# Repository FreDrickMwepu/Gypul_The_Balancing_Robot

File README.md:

# Robo Core Zambia

<p align="center">

</p>

## The Vision 🎯

I've been working on creating **RoboCore Zambia** — a locally engineered, modular robotics and embedded systems development platform designed for STEM education across Zambia and Africa. The goal is ambitious but necessary: build an affordable, open-source platform that enables educators and makers to teach robotics, IoT, and embedded systems design without relying on expensive imported kits (which typically cost $120–$700 or more, before shipping and customs).

RoboCore Zambia isn't a single application — it's a flexible foundation. Self-balancing robots, autonomous vehicles, drone controllers, IoT sensors, and wireless communication projects are all possible with the same core platform.

<p align="center">
	
	<br><em>Early prototype demonstrating the RoboCore Zambia platform</em>
</p>

The platform includes:
- 🧠 ESP32 microcontroller for processing and wireless communication
- 📡 IMU sensors (MPU-6050) for motion sensing and orientation tracking
- 🔌 Dual H-bridge motor drivers with high-current capability
- 🧩 Custom 2-layer PCB for integrated control and reliability
- 🧱 Modular connectors for motors, sensors, and expansions
- 🏭 Open-source design files for local manufacturing and customization

---

## Table of Contents 🗂️

- [The Vision](#the-vision-)
- [Why This Matters](#why-this-matters-)
- [Showcase Gallery](#showcase-gallery-)
- [The Reality Check](#the-reality-check-)
- [My Learning Curve](#my-learning-curve-)
- [How You Can Help](#how-you-can-help-)
- [The Bigger Picture](#the-bigger-picture-)
- [Next Steps](#next-steps-)
- [Get Involved](#get-involved-)
- [Final Thoughts](#final-thoughts-)

## Why This Matters 🌍

Since 2022, I've had the incredible privilege of impacting over 8000+ young people across Zambia through various programs covering digital literacy, robotics, and Artificial Intelligence. Every time I run these sessions, I see the same thing: brilliant, curious minds hungry to learn and create, but limited by access to affordable tools and platforms.

Most robotics kits are either impossible to import affordably to our markets or simply don't exist here. When they do make it through, the costs are prohibitive for most students, schools, and even makerspaces. This project aims to change that by creating something locally relevant, affordable, and designed specifically for our context.

## Showcase Gallery 📸

<details>
	<summary>More photos</summary>
	
</details>

---

## The Reality Check 🧪

Here's where I get honest about my learning journey (and current challenges):

**What's Working ✅:**

The core platform is functional! I've successfully built working prototypes and validated the PCB design with real-world testing. The ESP32-based control system, motor drivers, and IMU sensor integration all perform as expected. The modularity of the design means the same platform has been used for multiple applications beyond self-balancing robots.

<p align="center">
	
	<br><em>Robot balancing in action</em>
</p>

**What's Not Working ⚠️:**
- Some mechanical designs need optimization for different applications (weight distribution, center of gravity)
- Sensor calibration requires careful tuning depending on the specific use case
- Documentation and example code could be more comprehensive for different robot designs

**What's Still in Development 🛠️:**
- Expanding example code and tutorials for different robotics applications
- Developing reference designs for various platforms (balancing robots, autonomous rovers, drone controllers)
- Creating comprehensive educational resources and lesson plans
- Building a community repository of user-contributed designs and modifications

<p align="center">
	
	<br><em>PCB and mechanical design concepts</em>
</p>

## My Learning Curve 📈

I should be upfront: I'm no expert in any of these technical branches. 3D modeling, PCB design, control systems, embedded programming - this project and others I've worked on have all been massive learning experiences. Every "failure" has taught me something valuable, but I've definitely hit the point where I could use guidance from people who've walked this path before.

This isn't about admitting defeat - it's about recognizing that complex projects benefit from community knowledge and collaboration. Some of my best learning has come from bouncing ideas off people who see things I miss or approach problems differently.

## How You Can Help 🤝

I'm looking for any kind of support, and it doesn't have to be a huge commitment:

**Technical Guidance 🛠️:**
- PCB design feedback, manufacturing best practices, and component selection
- Embedded systems and firmware optimization
- Mechanical design and 3D printing techniques
- Educational curriculum integration for robotics and embedded systems
- Code review for control algorithms and sensor fusion

**Knowledge Sharing 📚:**
- Pointing me toward useful resources, tutorials, or documentation
- Sharing your own project experiences and lessons learned
- Connecting me with others who might be interested in collaborating

**Brainstorming 🧠:**
- Manufacturing and scaling strategies
- Educational curriculum integration ideas
- Distribution and partnership opportunities

**Community Building 🌱:**
- Spreading the word about the project
- Connecting me with educational institutions or maker communities
- Sharing this with anyone who might be interested in African tech innovation

## The Bigger Picture 🌐

This isn't just about building robotics projects — it's about creating an open-source, locally relevant development platform that enables education and innovation across the continent. The vision includes:

- Open-source hardware and firmware that others can fork, modify, and improve
- Educational resources, tutorials, and reference designs for common applications
- Partnerships with schools, universities, and maker spaces for curriculum integration
- A pathway for local component sourcing and PCB fabrication across African regions
- Community-driven documentation and a repository of user projects and innovations

Every learning moment, every component test, every design iteration gets us closer to something that can genuinely impact how young people across Africa engage with technology and innovation.

## Electronics & Hardware Design

### Overview

To move the project beyond breadboards and jump-wires we designed a custom 2-layer PCB in KiCad. The board replaces fragile prototype wiring to improve reliability, reduce assembly time, and lower per-unit costs — all important for classroom and makerspace use.

### Key Subsystems

- **Processing & Control:** ESP32-WROOM module providing Wi‑Fi, Bluetooth, and Arduino-compatible development for students and makers.
- **Motion Sensing:** MPU‑6050 IMU (3‑axis gyroscope + 3‑axis accelerometer) used for balance sensing and closed‑loop control.
- **Motor Control:** Dual H‑bridge motor drivers with dedicated high‑current copper traces and thermal considerations for continuous operation.
- **Power Management:** LiPo battery support with a USB Type‑C charging input, onboard voltage regulators, and reverse‑polarity protection to protect classroom hardware.
- **Memory:** Onboard flash for firmware and simple data logging (sensor logs, calibration presets).
- **Connectivity & Expansion:** Standard I2C, SPI, and UART breakout headers plus modular connectors (J2, J3, J4) for motors and external sensors to keep the design flexible.

### Design Decisions

- Chosen parts prioritize local availability and low BOM complexity to make sourcing components easier in Zambia and nearby markets.
- A continuous ground plane and careful keep‑out were used around the ESP32 antenna to preserve wireless performance.
- Power traces for motors were routed and sized separately from logic power to reduce noise and avoid voltage drops during high current draw.
- Breakout headers and modular connectors were added to encourage experimentation and easy repairs in an educational setting.

### Toolchain

The PCB was designed in KiCad. 3D renders were generated from the PCB model to validate component placement and mechanical fit before fabrication.

### Status

The board is at Revision 1 and currently in fabrication and early testing. Feedback from these tests will guide revisions to the layout and BOM.

For full schematics, PCB layout files, and fabrication notes see the project hardware folder: [PCB-Design](PCB-Design).

### Board Renders

<em>Top and bottom 3D renders of the RoboCore PCB. Replace these placeholder files with the actual KiCad export renders in the `PCB-Design` folder.</em>

## Get Involved 📣

If any of this resonates with you - whether you're a technical expert, educator, maker, or just someone who believes in making technology more accessible - I'd love to connect.

You can reach me through:
- This platform (just send a message!)
- Website: [www.plastalbotbuilders.com](https://plastalbot.comon.tech/home)
- Email: fredrickmwepu22@gmail.com

Even if you can't directly contribute technical expertise, sharing this project, connecting me with others, or just offering encouragement makes a real difference.

## Final Thoughts 💡

Building RoboCore Zambia has been humbling, educational, and incredibly motivating. Every challenge reminds me why this work matters — because somewhere, a young person is waiting for the chance to learn, build, and innovate, and we have the opportunity to make that possible.

<p align="center">
	
	<br><em>Click image to watch a short demo video</em>
</p>

Thanks for taking the time to read this, and thanks in advance for any way you choose to support this journey. Together, we can build an open-source robotics platform that empowers the next generation of African innovators, engineers, and educators.

---

*This project represents just one piece of the larger puzzle of making technology education accessible across Africa. Every contribution, no matter how small, helps build that future.*

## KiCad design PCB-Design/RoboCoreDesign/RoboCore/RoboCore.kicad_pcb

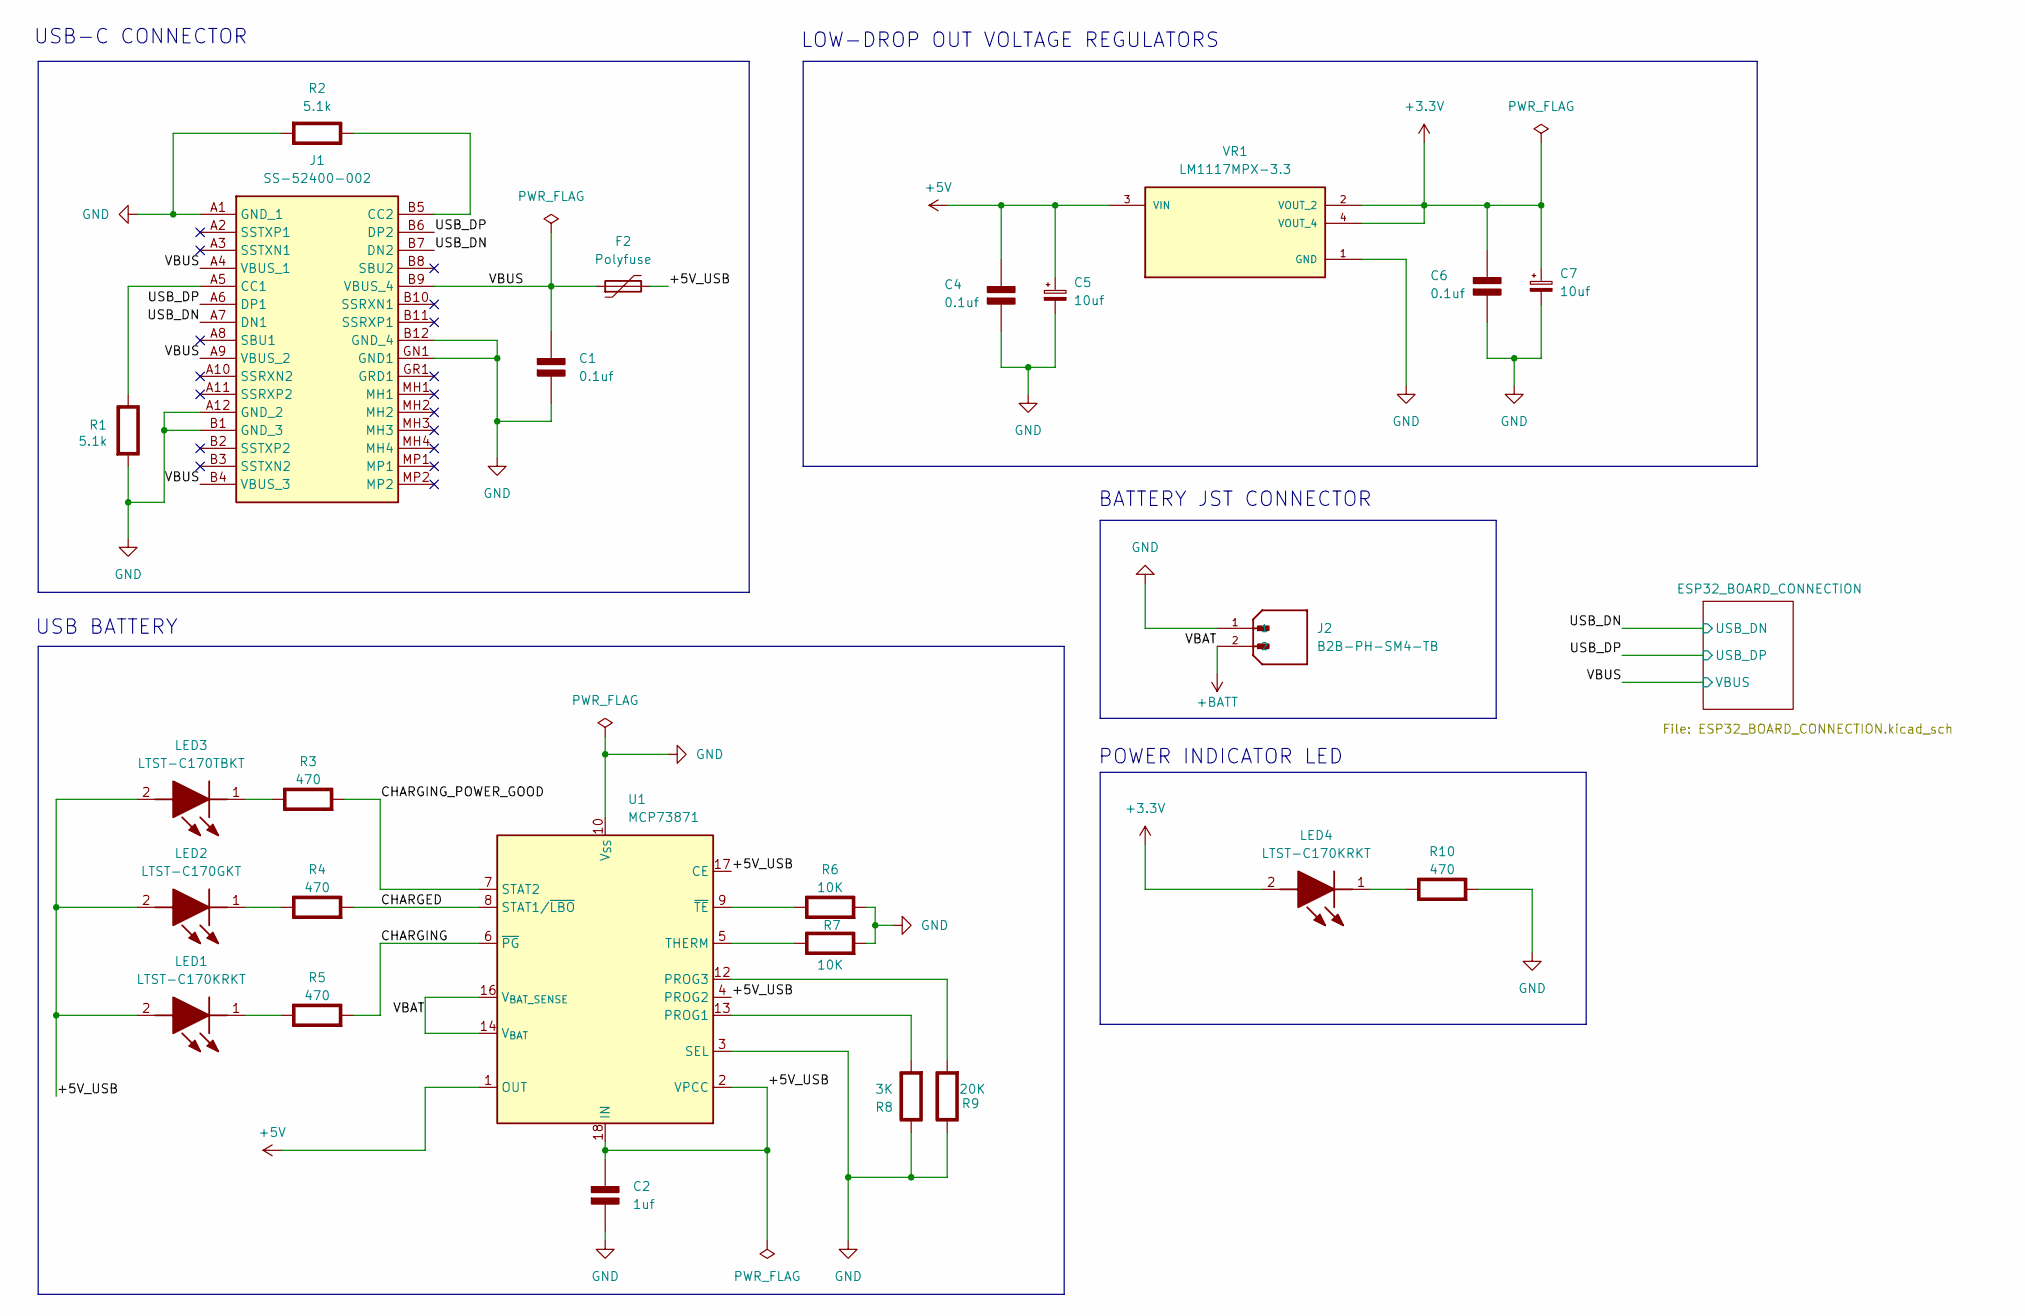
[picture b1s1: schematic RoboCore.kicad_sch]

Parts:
C1, C4, C6: 0.1uf; C_0805_2012Metric; Rating V
C2: 1uf; C_0805_2012Metric; Rating V
C5, C7: 10uf; T491A
F2: Polyfuse; FUSSC324X455X250-2N
J1: SS-52400-002; SS52400002; Manufacturer_Part_Number SS-52400-002; Mouser Part Number 530-SS-52400-002
J2: B2B-PH-SM4-TB; JST_B2B-PH-SM4-TB; PARTREV N/A
LED1, LED4: LTST-C170KRKT; LEDC2012X120N; Manufacturer_Part_Number LTST-C170KRKT; Mouser Part Number 859-LTST-C170KRKT
LED2: LTST-C170GKT; LEDC2012X120N; Manufacturer_Part_Number LTST-C170GKT; Mouser Part Number 859-LTST-C170GKT
LED3: LTST-C170TBKT; LEDC2012X120N; Manufacturer_Part_Number LTST-C170TBKT; Mouser Part Number 859-LTST-C170TBKT
R1, R2: 5.1k; R_0805_2012Metric; Rating W
R3, R4, R5, R10: 470; R_0805_2012Metric; Rating W
R6, R7: 10K; R_0805_2012Metric; Rating W
R8: 3K; R_0805_2012Metric; Rating W
R9: 20K; R_0805_2012Metric; Rating W
U1: MCP73871; QFN-20-1EP_4x4mm_P0.5mm_EP2.5x2.5mm
VR1: LM1117MPX-3.3; VREG_LM1117MPX-3.3_NOPB

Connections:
+5V: C4.1 (+), C5.1, U1.1 (OUT), U1.20 (OUT), VR1.3 (VIN)
/+5V_USB: C2.1 (+), F2.2, LED1.2 (A), LED2.2 (A), LED3.2 (A), U1.2 (VPCC), U1.4 (PROG2), U1.17 (CE), U1.18 (IN), U1.19 (IN)
/CHARGED: R4.2 (-), U1.8 (STAT1/~LBO)
/CHARGING: R5.2 (-), U1.6 (~PG)
/CHARGING_POWER_GOOD: R3.2 (-), U1.7 (STAT2)
/USB_DN: J1.A7 (DN1), J1.B7 (DN2); also elsewhere on the board
/USB_DP: J1.A6 (DP1), J1.B6 (DP2); also elsewhere on the board
/VBAT: J2.2, U1.14 (V_{BAT}), U1.15 (V_{BAT}), U1.16 (V_{BAT_SENSE})
/VBUS: C1.1 (+), F2.1, J1.A4 (VBUS_1), J1.A9 (VBUS_2), J1.B4 (VBUS_3), J1.B9 (VBUS_4); also elsewhere on the board
unnamed: J1.A5 (CC1), R1.1 (+)
unnamed: J1.B5 (CC2), R2.1 (+)
unnamed: LED1.1 (K), R5.1 (+)
unnamed: LED2.1 (K), R4.1 (+)
unnamed: LED3.1 (K), R3.1 (+)
unnamed: LED4.1 (K), R10.1 (+)
unnamed: R6.1 (+), U1.9 (~TE)
unnamed: R7.1 (+), U1.5 (THERM)
unnamed: R8.2 (-), U1.13 (PROG1)
unnamed: R9.2 (-), U1.12 (PROG3)

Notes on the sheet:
USB BATTERY
POWER INDICATOR LED
BATTERY JST CONNECTOR
LOW-DROP OUT VOLTAGE REGULATORS
USB-C CONNECTOR

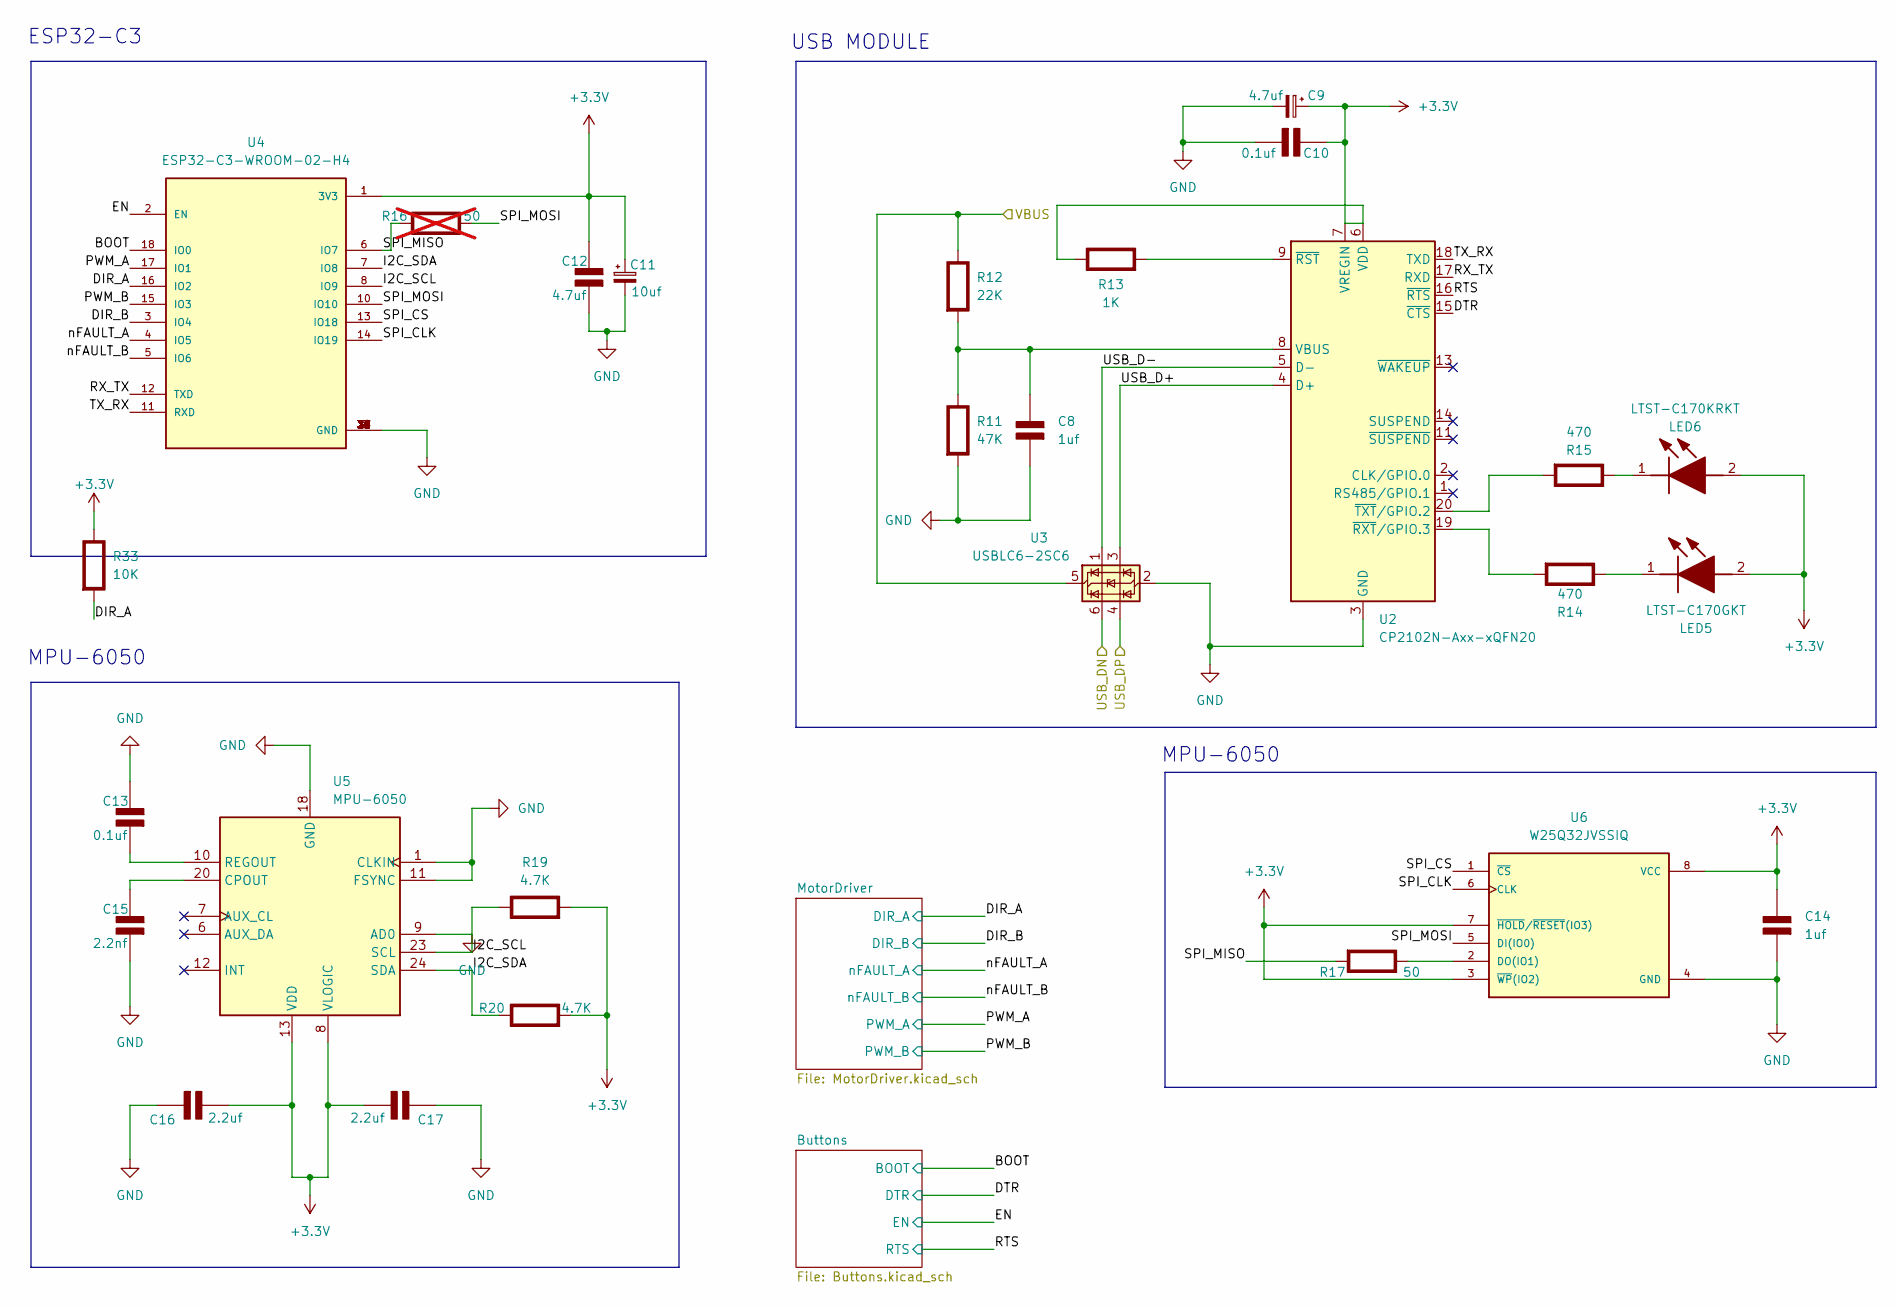
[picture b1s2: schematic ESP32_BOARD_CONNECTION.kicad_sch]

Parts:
C8, C14: 1uf; C_0805_2012Metric; Rating V
C9: 4.7uf; T491A
C10, C13: 0.1uf; C_0805_2012Metric; Rating V
C11: 10uf; T491A
C12: 4.7uf; C_0805_2012Metric; Rating V
C15: 2.2nf; C_0805_2012Metric; Rating V
C16, C17: 2.2uf; C_0805_2012Metric; Rating V
LED5: LTST-C170GKT; LEDC2012X120N; Manufacturer_Part_Number LTST-C170GKT; Mouser Part Number 859-LTST-C170GKT
LED6: LTST-C170KRKT; LEDC2012X120N; Manufacturer_Part_Number LTST-C170KRKT; Mouser Part Number 859-LTST-C170KRKT
R11: 47K; R_0805_2012Metric; Rating W
R12: 22K; R_0805_2012Metric; Rating W
R13: 1K; R_0805_2012Metric; Rating W
R14, R15: 470; R_0805_2012Metric; Rating W
R16: 50; R_0805_2012Metric; Rating W; not fitted
R17: 50; R_0805_2012Metric; Rating W
R19, R20: 4.7K; R_0805_2012Metric; Rating W
R33: 10K; R_0805_2012Metric
U2: CP2102N-Axx-xQFN20; QFN50P400X400X100-21N-D
U3: USBLC6-2SC6; SOT-23-6
U4: ESP32-C3-WROOM-02-H4; MODULE_ESP32-C3-WROOM-02-H4
U5: MPU-6050; InvenSense_QFN-24_4x4mm_P0.5mm
U6: W25Q32JVSSIQ; SOIC127P790X216-8N; M_PART_NUMBER W25QXX

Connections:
/ESP32_BOARD_CONNECTION/BOOT: U4.18 (IO0); also elsewhere on the board
/ESP32_BOARD_CONNECTION/DIR_A: R33.2 (-), U4.16 (IO2); also elsewhere on the board
/ESP32_BOARD_CONNECTION/DIR_B: U4.3 (IO4); also elsewhere on the board
/ESP32_BOARD_CONNECTION/DTR: U2.15 (~CTS); also elsewhere on the board
/ESP32_BOARD_CONNECTION/EN: U4.2 (EN); also elsewhere on the board
/ESP32_BOARD_CONNECTION/PWM_A: U4.17 (IO1); also elsewhere on the board
/ESP32_BOARD_CONNECTION/PWM_B: U4.15 (IO3); also elsewhere on the board
/ESP32_BOARD_CONNECTION/RTS: U2.16 (~RTS); also elsewhere on the board
/ESP32_BOARD_CONNECTION/RX_TX: U2.17 (RXD), U4.12 (TXD)
/ESP32_BOARD_CONNECTION/SPI_CLK: U4.14 (IO19), U6.6 (CLK)
/ESP32_BOARD_CONNECTION/SPI_CS: U4.13 (IO18), U6.1 (~CS)
/ESP32_BOARD_CONNECTION/SPI_MOSI: R16.2 (-), U4.10 (IO10), U6.5 (DI(IO0))
/ESP32_BOARD_CONNECTION/TX_RX: U2.18 (TXD), U4.11 (RXD)
/ESP32_BOARD_CONNECTION/USB_D+: U2.4 (D+), U3.3 (I/O2)
/ESP32_BOARD_CONNECTION/USB_D-: U2.5 (D-), U3.1 (I/O1)
/ESP32_BOARD_CONNECTION/nFAULT_A: U4.4 (IO5); also elsewhere on the board
/ESP32_BOARD_CONNECTION/nFAULT_B: U4.5 (IO6); also elsewhere on the board
/USB_DN: U3.6 (I/O1); also elsewhere on the board
/USB_DP: U3.4 (I/O2); also elsewhere on the board
/VBUS: R12.1 (+), U3.5 (VBUS); also elsewhere on the board
unnamed: C8.2 (-), R11.1 (+), R12.2 (-), U2.8 (VBUS)
unnamed: C13.1 (+), U5.10 (REGOUT)
unnamed: C15.2 (-), U5.20 (CPOUT)
unnamed: LED5.1 (K), R14.1 (+)
unnamed: LED6.1 (K), R15.1 (+)
unnamed: R13.2 (-), U2.9 (~RST)
unnamed: R14.2 (-), U2.19 (~RXT/GPIO.3)
unnamed: R15.2 (-), U2.20 (~TXT/GPIO.2)
unnamed: R17.1 (+), U6.2 (DO(IO1))

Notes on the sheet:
USB MODULE
ESP32-C3
MPU-6050

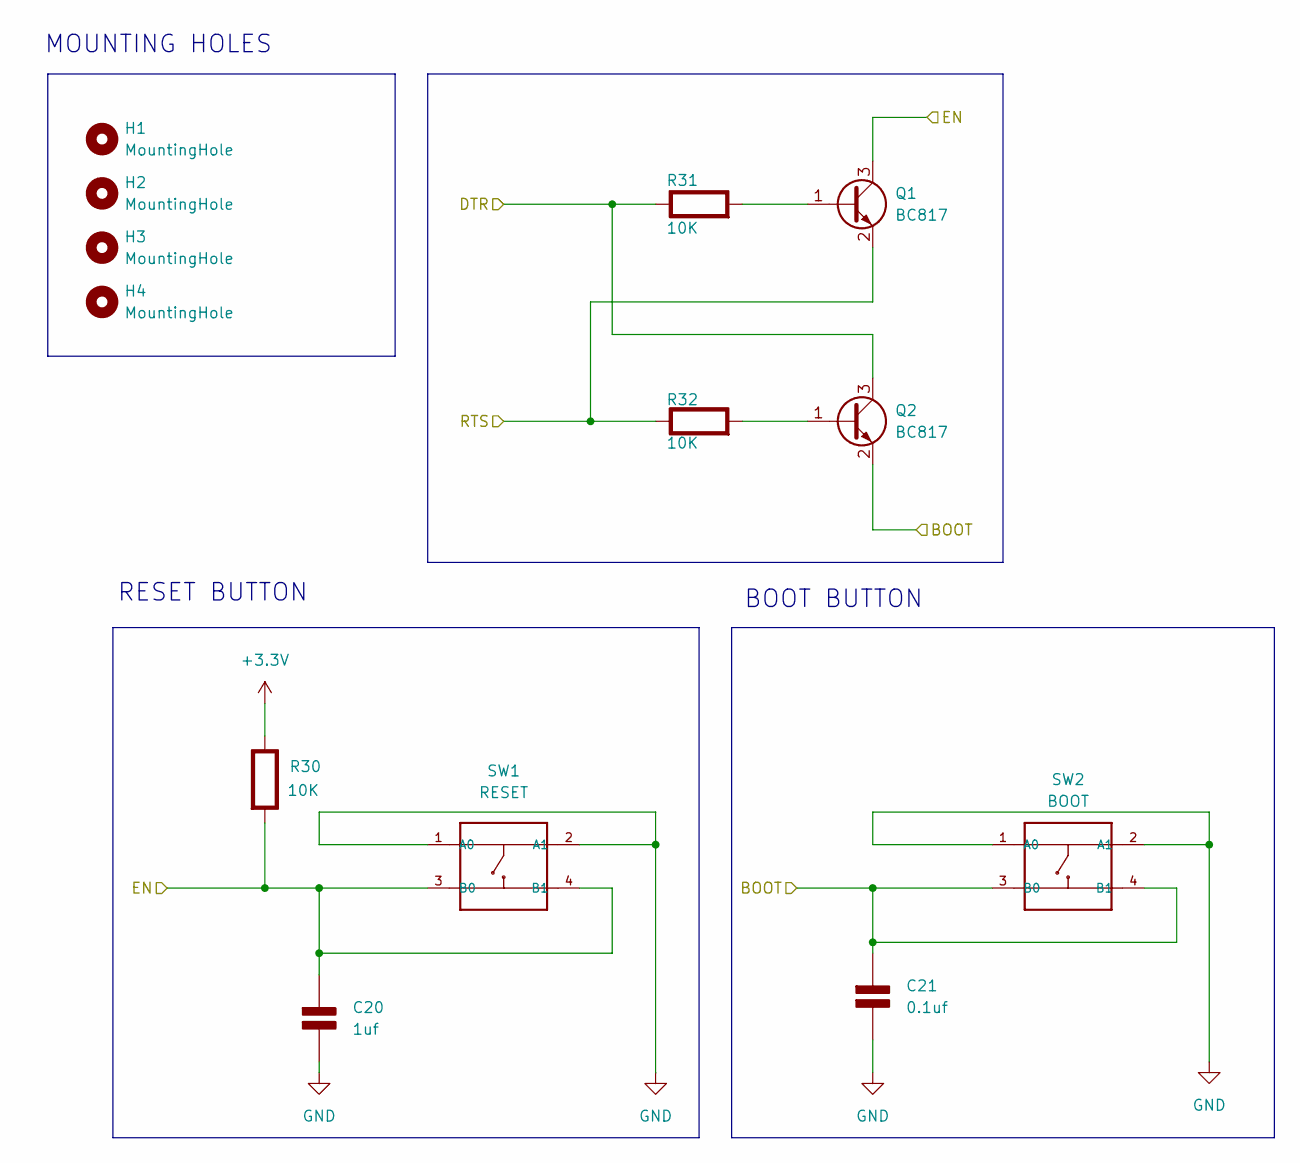
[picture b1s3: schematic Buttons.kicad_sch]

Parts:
C20: 1uf; C_0805_2012Metric; Rating V
C21: 0.1uf; C_0805_2012Metric; Rating V
H1, H2, H3, H4: MountingHole; MountingHole_2mm
Q1, Q2: BC817; SOT-23
R30, R31, R32: 10K; R_0805_2012Metric; Rating W
SW1: RESET; SW4-SMD-5.2X5.2X1.5MM
SW2: BOOT; SW4-SMD-5.2X5.2X1.5MM

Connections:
/ESP32_BOARD_CONNECTION/BOOT: C21.1 (+), Q2.2 (E), SW2.3 (B0), SW2.4 (B1); also elsewhere on the board
/ESP32_BOARD_CONNECTION/DTR: Q2.3 (C), R31.1 (+); also elsewhere on the board
/ESP32_BOARD_CONNECTION/EN: C20.1 (+), Q1.3 (C), R30.2 (-), SW1.3 (B0), SW1.4 (B1); also elsewhere on the board
/ESP32_BOARD_CONNECTION/RTS: Q1.2 (E), R32.1 (+); also elsewhere on the board
unnamed: Q1.1 (B), R31.2 (-)
unnamed: Q2.1 (B), R32.2 (-)

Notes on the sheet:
MOUNTING HOLES
RESET BUTTON
BOOT BUTTON

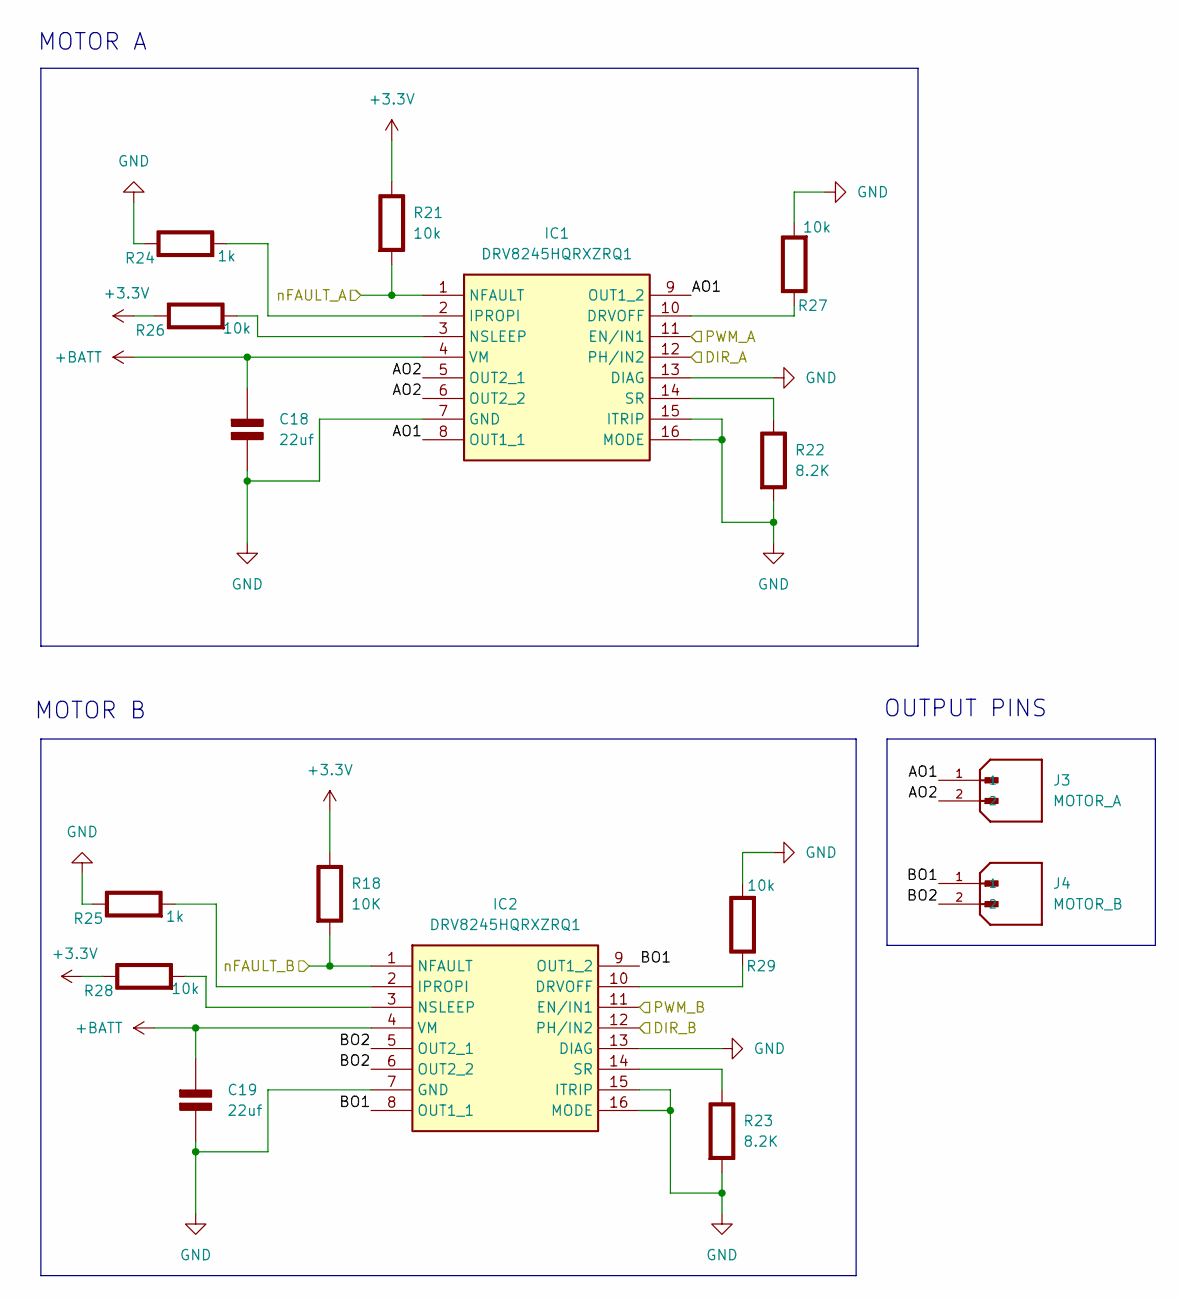
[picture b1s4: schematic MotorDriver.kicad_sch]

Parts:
C18, C19: 22uf; C_0805_2012Metric; Rating V
IC1, IC2: DRV8245HQRXZRQ1; Manufacturer_Part_Number DRV8245HQRXZRQ1; Mouser Part Number 595-DRV8245HQRXZRQ1
J3: MOTOR_A; JST_B2B-PH-SM4-TB; PARTREV N/A
J4: MOTOR_B; JST_B2B-PH-SM4-TB; PARTREV N/A
R18: 10K; R_0805_2012Metric; Rating W
R21, R26, R27, R28, R29: 10k; R_0805_2012Metric; Rating W
R22, R23: 8.2K; R_0805_2012Metric; Rating W
R24, R25: 1k; R_0805_2012Metric; Rating W

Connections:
+BATT: C18.1 (+), C19.1 (+), IC1.4 (VM), IC2.4 (VM)
/ESP32_BOARD_CONNECTION/DIR_A: IC1.12 (PH/IN2); also elsewhere on the board
/ESP32_BOARD_CONNECTION/DIR_B: IC2.12 (PH/IN2); also elsewhere on the board
/ESP32_BOARD_CONNECTION/MotorDriver/AO1: IC1.8 (OUT1_1), IC1.9 (OUT1_2), J3.1
/ESP32_BOARD_CONNECTION/MotorDriver/AO2: IC1.5 (OUT2_1), IC1.6 (OUT2_2), J3.2
/ESP32_BOARD_CONNECTION/MotorDriver/BO1: IC2.8 (OUT1_1), IC2.9 (OUT1_2), J4.1
/ESP32_BOARD_CONNECTION/MotorDriver/BO2: IC2.5 (OUT2_1), IC2.6 (OUT2_2), J4.2
/ESP32_BOARD_CONNECTION/PWM_A: IC1.11 (EN/IN1); also elsewhere on the board
/ESP32_BOARD_CONNECTION/PWM_B: IC2.11 (EN/IN1); also elsewhere on the board
/ESP32_BOARD_CONNECTION/nFAULT_A: IC1.1 (NFAULT), R21.2 (-); also elsewhere on the board
/ESP32_BOARD_CONNECTION/nFAULT_B: IC2.1 (NFAULT), R18.2 (-); also elsewhere on the board
unnamed: IC1.10 (DRVOFF), R27.1 (+)
unnamed: IC1.2 (IPROPI), R24.2 (-)
unnamed: IC1.3 (NSLEEP), R26.2 (-)
unnamed: IC1.14 (SR), R22.1 (+)
unnamed: IC2.10 (DRVOFF), R29.1 (+)
unnamed: IC2.2 (IPROPI), R25.2 (-)
unnamed: IC2.3 (NSLEEP), R28.2 (-)
unnamed: IC2.14 (SR), R23.1 (+)

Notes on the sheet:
MOTOR A
OUTPUT PINS
MOTOR B

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
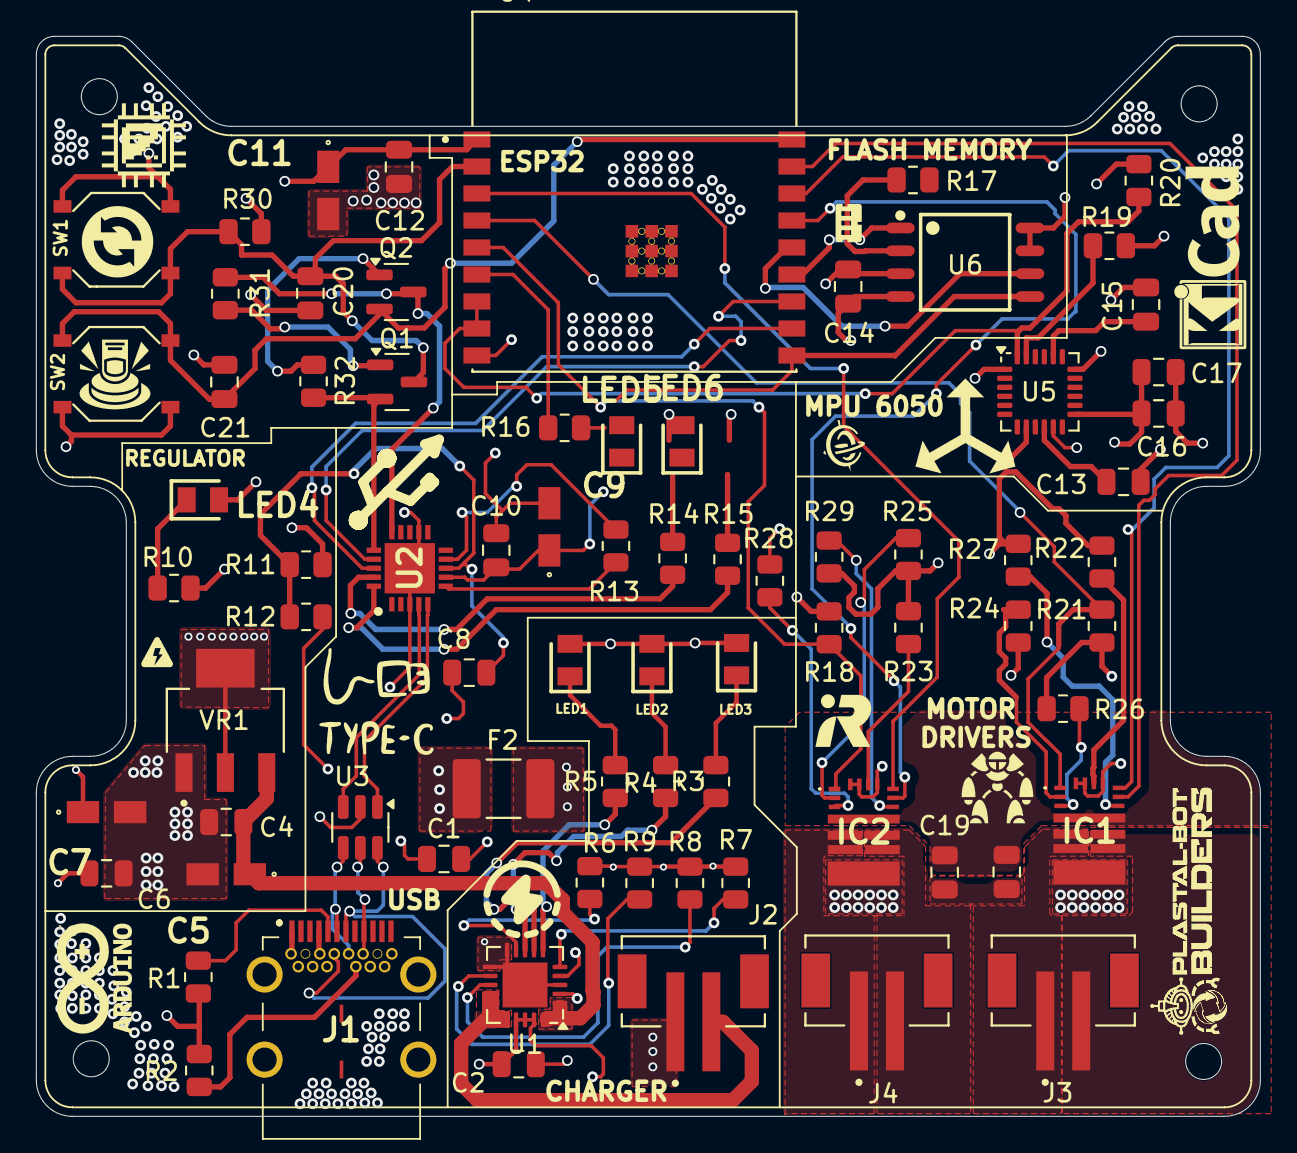
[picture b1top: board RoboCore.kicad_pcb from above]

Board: 4 copper layers, 68.0 x 60.0 mm, 80 parts (0 on the bottom side), 66 nets.

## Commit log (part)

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2025-09-02 added media files to the repository
2025-09-02 docs: enhance README with images and demo video
2025-09-02 docs(README): add badges, gallery, emojis, and checklist formatting
2025-11-13 fix(README): correct href attribute in GitHub stars badge
2025-11-15 Managed to find the data sheets, Footprints and schematic symbols for most of the components that I will need for the board.
2025-11-16 added mot of the things that are needed
2025-11-21 Add new data sheets and update existing ones in PCB-Design/Data_Sheets
    - Added new data sheets for various components:
    - ML Microchip Technology
    - PESD5V0S1UL,315 NXP Semiconductors
    - ESP32-S3-DevKitC-1
    - SKQGADE010 ALPS
    - TEMT6000X01 Vishay Semiconductor
2025-11-28 Add initial PCB and schematic files for RoboCore Design
    - Created RoboCore_Design.kicad_pcb with initial board setup.
    - Added RoboCore_Design.kicad_prl for project settings and visibility options.
    - Introduced RoboCore_Design.kicad_pro containing design settings and net configurations.
    - Established RoboCore_Design.kicad_sch for schematic representation with UUID and paper size.
    - Included fp-info-cache and lock files for footprint and session management.
    - Added backup zip file for Untitled project with multiple design files.
2025-11-29 Add new symbols for ESP32-C3-WROOM-02-H4 and USBLC6-2SC6 components; include detailed properties and pin configurations
2025-11-30 Remove unnecessary .DS_Store files from the repository
2025-11-30 Add footprint and symbol for KEMET T491A475K010AT tantalum capacitor
    - Created a new footprint CAPMP3216X180N for the KEMET T491A475K010AT capacitor, including SMD pads and fabrication details.
    - Added a corresponding symbol for T491A475K010AT in the library, including properties such as reference, value, footprint, manufacturer, and availability.
2025-11-30 Remove unnecessary .DS_Store files from PCB-Design and Libraries directories
2025-12-05 Remove unnecessary .DS_Store file from PCB-Design directory
2025-12-25 Added the KiCad Files
2026-01-02 Refactor code structure for improved readability and maintainability
2026-01-05 made improvements to the PCB
2026-01-05 made more changes to the board
2026-01-05 a few changes to the board's layout
2026-01-05 made more changes
2026-01-06 made to finish the component routing
2026-01-07 zip file update
2026-01-11 made improvements to the motor copper power, signal planes
2026-01-12 made a few changes yesterday night that I forgot to commit
2026-01-18 another attempt at correcting the errors but i've yet again failed terribly
2026-05-20 Updated RoboCore PCB design and assets
2026-05-28 Added board graphics
2026-05-28 Add images and update README for RoboCore Zambia project

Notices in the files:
README.md:
License: MIT
